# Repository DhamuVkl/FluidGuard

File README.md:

<br/>
<p align="center">

  <h1 align="center">FluidGuard</h1>

  <p align="center">
    Envision a helpful companion that not only observes fluid levels but also takes proactive measures to prevent wastage and shortages!
    <br/>
    <br/>
  </p>
</p>

## Table Of Contents

* [About the Project](#about-the-project)
* [Key Features](#key-features)
* [Technologies Used](#technologies-used)
* [Schematics and Fabrication](#schematics-and-fabrication)
* [Roadmap](#roadmap)
* [Contributing](#contributing)
* [License](#license)
* [Conclusion](#conclusion)
* [Author](#author)

## About The Project

 <font size= “1”> **The FluidGuard:** </font> Intelligent Liquid Level Management and Refill Solution is akin to having a smart assistant for effectively managing liquids in tanks and containers. Envision a helpful companion that not only observes fluid levels but also takes proactive measures to prevent wastage and shortages, all the while being remarkably dependable and comprehensible. It tackles the challenges associated with manual fluid level management by seamlessly integrating an array of sensors, microcontrollers, wireless communication modules, and control mechanisms. This integration results in a sophisticated approach to fluid monitoring and regulation. Its significance shines in scenarios where precise fluid level management proves pivotal, such as within industrial, agricultural, and distant locations.

##  Key Features: 

*	**Real-time Fluid Level Monitoring:** This system is engineered to monitor liquid levels across various environments, ranging from water tanks to industrial storage. By constantly gathering data from the fluid level sensor, it achieves precise and up-to-the-minute monitoring of fluid levels.
  
*	**Fail-safe Mechanisms:** To guarantee the system's integrity, fail-safe mechanisms are integrated. These mechanisms address potential issues such as data loss or transmission failures, ensuring the system remains operational and dependable.
  
*	**Error Detection and Correction:** The system's intelligence extends to error detection and real-time correction. It can identify sensor errors and implement corrective actions, contributing to its reliability and accuracy.
  
*	**Wireless Communication:** The NRF24L01+ PA/LNA modules serve as the communication backbone between the transmitting and receiving devices. These modules operate on a reliable wireless protocol, enabling seamless data transmission over distances, even in challenging environments.

*	**Automated Fluid Regulation:** Through relay components, the system automatically controls the pump to maintain fluid levels within pre-defined thresholds. This ensures efficient resource utilization and prevents overflows or depletion of the fluid source.
  
*	**User-friendly Interface:** The project incorporates a 16x2 LCD display that presents fluid levels visually using bars and percentages. This intuitive interface enhances user experience and simplifies the interpretation of fluid data.
  
*	**Versatility Across Storage Scenarios:** The system's adaptability makes it suitable for various storage scenarios, including silos and distant locations. Its wireless nature ensures that fluid data can be accessed and managed from a central location, saving time and resources.

## Technologies Used:

*	**Microcontroller (Atmega 328p):** The microcontroller serves as the project's core, processing data from the sensor and facilitating communication with the wireless module.
  
*	**Wireless Communication (NRF24L01+ PA/LNA):**  These wireless modules are responsible for transmitting fluid level data from the transmitting device to the receiving device. The PA/LNA feature enhances the communication range and signal strength.
  
*	**Fluid Level Sensor (HC-SR04):** The HC-SR04 ultrasonic sensor accurately measures fluid levels. It emits ultrasonic signals and calculates the time taken for the signal to bounce back, providing a precise measurement of the distance to the fluid's surface.
  
*	**User Interface (16x2 LCD Display):** The LCD display translates numerical data into visual information, showing fluid levels in both bars and percentages. It offers an accessible way for users to interpret the data.
  
*	**Pump Control (Relay):** The relay component controls the pump's operation based on the received fluid level data. It ensures that the fluid level is maintained within the desired range.

## Schematics and Fabrication
### FluidGuard-RX

### FluidGuard-TX

## Roadmap

See the [open issues](https://github.com/dhamuvkl/FluidGuard/issues) for a list of proposed features (and known issues).

## Contributing

Contributions are what make the open source community such an amazing place to be learn, inspire, and create. Any contributions you make are **greatly appreciated**.
* If you have suggestions for adding or removing projects, feel free to [open an issue](https://github.com/dhamuvkl/FluidGuard/issues/new) to discuss it, or directly create a pull request after you edit the *README.md* file with necessary changes.
* Please make sure you check your spelling and grammar.
* Create individual PR for each suggestion.

### Conclusion:

The Automated Liquid Level Indication and Refilling System is a testament to my proficiency in multiple domains, including microcontroller programming, wireless communication, sensor integration, and control mechanisms. By showcasing this project in my portfolio, I demonstrate my ability to develop innovative solutions that offer practical benefits in real-world scenarios. The fusion of technology, intelligent control, and user-friendly interfaces positions this project as a significant accomplishment in the field of automated fluid management.

## License

Distributed under the MIT License. See [LICENSE](https://github.com/dhamuvkl/FluidGuard/blob/main/LICENSE.md) for more information.

## Author

* **Dharageswaran S** - *Electronics Enthusiast | Innovator | Tech Visionary* - [Dharageswaran S](https://github.com/DhamuVkl/) - *Owner*

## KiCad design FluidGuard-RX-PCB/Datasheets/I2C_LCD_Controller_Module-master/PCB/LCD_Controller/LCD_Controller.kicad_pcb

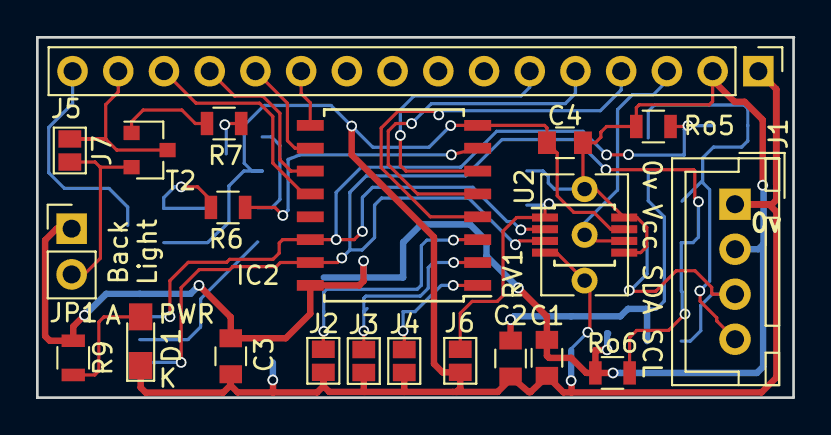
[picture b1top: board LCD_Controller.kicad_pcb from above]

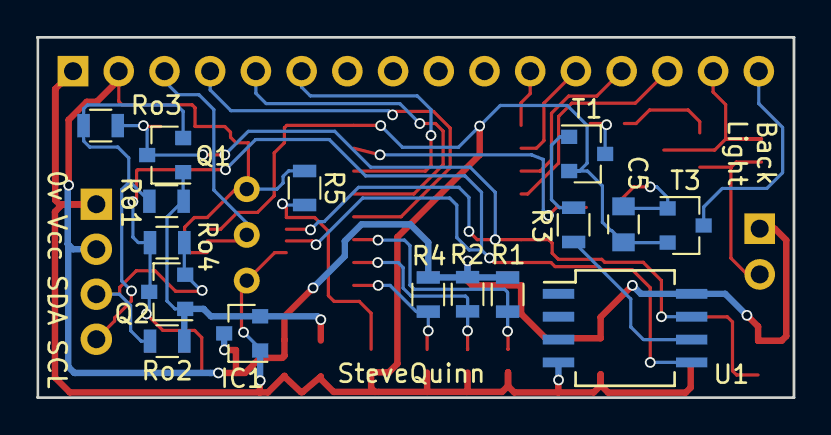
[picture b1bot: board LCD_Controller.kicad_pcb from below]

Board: 2 copper layers, 42.0 x 20.0 mm, 38 parts (16 on the bottom side), 29 nets.

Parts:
C1, C2: 1uF Ceramic; C_0805
C3, C4, C5: 0.1uF; C_0805
D1: RED LED; LED_0805_HandSoldering
IC1: XC6206; SOT-23
IC2: PCF8574A; SOIC-16W_7.5x10.3mm_Pitch1.27mm
J1: LCD; JST_XH_B04B-XH-A_04x2.50mm_Straight
J2, J3, J4, J6, J7: GS2
J5: To LCD; Pin_Header_Straight_1x16_Pitch2.54mm
JP1: Jumper; Pin_Header_Straight_1x02_Pitch2.54mm
Q1, Q2: DMG3414U; SOT-23
R1, R2, R4, R5: 10K; R_0805
R3, R6, R7, R9: 1K; R_0805
RV1: 10K; Potentiometer_Trimmer_Vishay_T73XW_Vertical
Ro1, Ro2, Ro5, Ro6: 4K7; R_0805
Ro3, Ro4: 0R; R_0805
T1, T3: BCW66GLT1G; SOT-23
T2: BC858C; SOT-23
U1: ATTINY85-20PU; SO-8_5.3x6.2mm_Pitch1.27mm
U2: MCP4561-103E/MS; MSOP-8_3x3mm_Pitch0.65mm

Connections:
+3V3: C2.2, IC1.2, Q1.1, Q2.1, Ro1.1, Ro2.1
+5V: C1.2, C3.2, C4.2, IC1.3, IC2.16, J1.2, J5.2, JP1.1, R1.1, R2.1, R4.1, R5.1, R9.1, RV1.1, Ro5.1, Ro6.1, U1.8, U2.5, U2.8
GND: C1.1, C2.1, C3.1, C4.1, C5.2, D1.1, IC1.1, IC2.8, J1.1, J2.2, J3.2, J4.2, J5.1, J6.2, RV1.3, T1.2, T3.2, U1.4, U2.4, U2.7
unnamed: C5.1, R6.1, T3.1
unnamed: D1.2, R9.2
unnamed: IC2.1, J4.1, R4.2
unnamed: IC2.2, J3.1, R2.2
unnamed: IC2.3, J2.1, R1.2
unnamed: IC2.4, J5.4
unnamed: IC2.5, J5.5
unnamed: IC2.6, J5.6
unnamed: IC2.7, R6.2
unnamed: IC2.9, J5.11
unnamed: IC2.10, J5.12
unnamed: IC2.11, J5.13
unnamed: IC2.12, J5.14
unnamed: J5.3, RV1.2, U2.6
unnamed: J5.15, J7.1, T2.3
unnamed: J5.16, T3.3
unnamed: J6.1, R5.2, U2.1
unnamed: J7.2, JP1.2, T2.2
unnamed: R3.1, T1.1
unnamed: R3.2, U1.6
unnamed: R7.1, T2.1
unnamed: R7.2, T1.3
SCL: J1.4, Q1.2, Ro1.2, Ro3.1
SCL_H: IC2.14, Q1.3, Ro3.2, Ro5.2, U1.7, U2.2
SDA: J1.3, Q2.2, Ro2.2, Ro4.1
SDA_H: IC2.15, Q2.3, Ro4.2, Ro6.2, U1.5, U2.3

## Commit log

2023-09-06 created hub
2023-09-06 trim
2023-09-07 redo
2023-09-07 initial
2023-09-07 version 1
2023-09-07 version 2
2023-09-07 added features
2023-09-07 V2.1
2023-09-07 V3.0
2023-09-07 added test files
2024-06-26 #Initializing
